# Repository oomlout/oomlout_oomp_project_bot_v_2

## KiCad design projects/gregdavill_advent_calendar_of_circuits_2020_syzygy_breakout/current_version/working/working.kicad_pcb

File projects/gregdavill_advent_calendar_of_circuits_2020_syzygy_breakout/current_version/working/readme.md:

# advent_calendar_of_circuits_2020
 
## summary 
* id: gregdavill_advent_calendar_of_circuits_2020_syzygy_breakout
* user: gregdavill
* name: advent_calendar_of_circuits_2020
* board: syzygy_breakout
* repo: https://github.com/gregdavill/advent-calendar-of-circuits-2020
* src_file_repo_kicad_pcb: syzygy-breakout/kicad-src/syzygy-breakout.kicad_pcb
* src_file_repo_kicad_pcb_link: https://github.com/gregdavill/advent-calendar-of-circuits-2020/tree/main/syzygy-breakout/kicad-src/syzygy-breakout.kicad_pcb
* src_file_repo_kicad_sch: syzygy-breakout/kicad-src/p-mcu.kicad_sch
* src_file_repo_kicad_sch_link: https://github.com/gregdavill/advent-calendar-of-circuits-2020/tree/main/syzygy-breakout/kicad-src/p-mcu.kicad_sch

* src_file_repo_sch: 
* src_file_repo_sch_link: https://github.com/gregdavill/advent-calendar-of-circuits-2020/tree/main/
* full details link: https://github.com/oomlout/oomlout_oomp_project_bot_v_2/tree/main/projects/gregdavill_advent_calendar_of_circuits_2020_syzygy_breakout/current_version/working

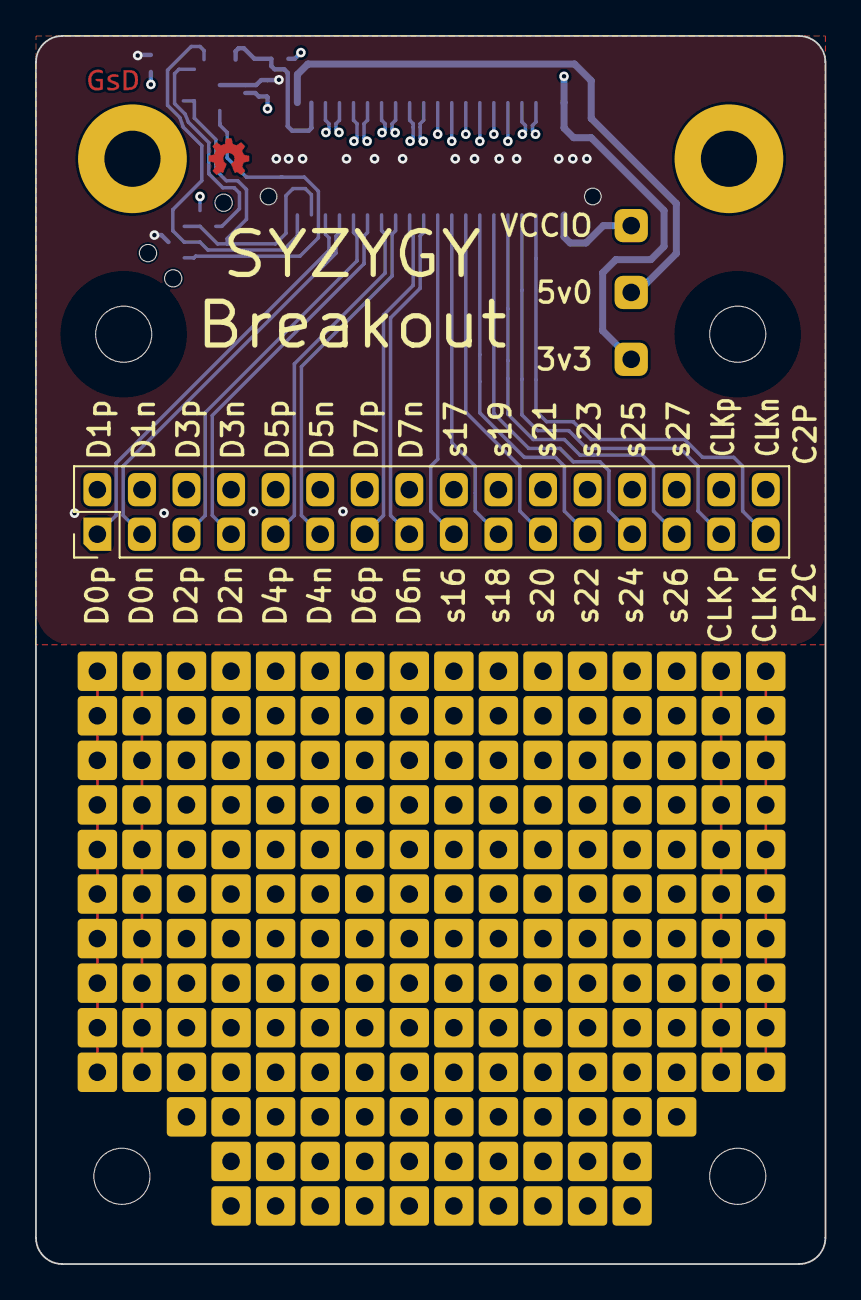
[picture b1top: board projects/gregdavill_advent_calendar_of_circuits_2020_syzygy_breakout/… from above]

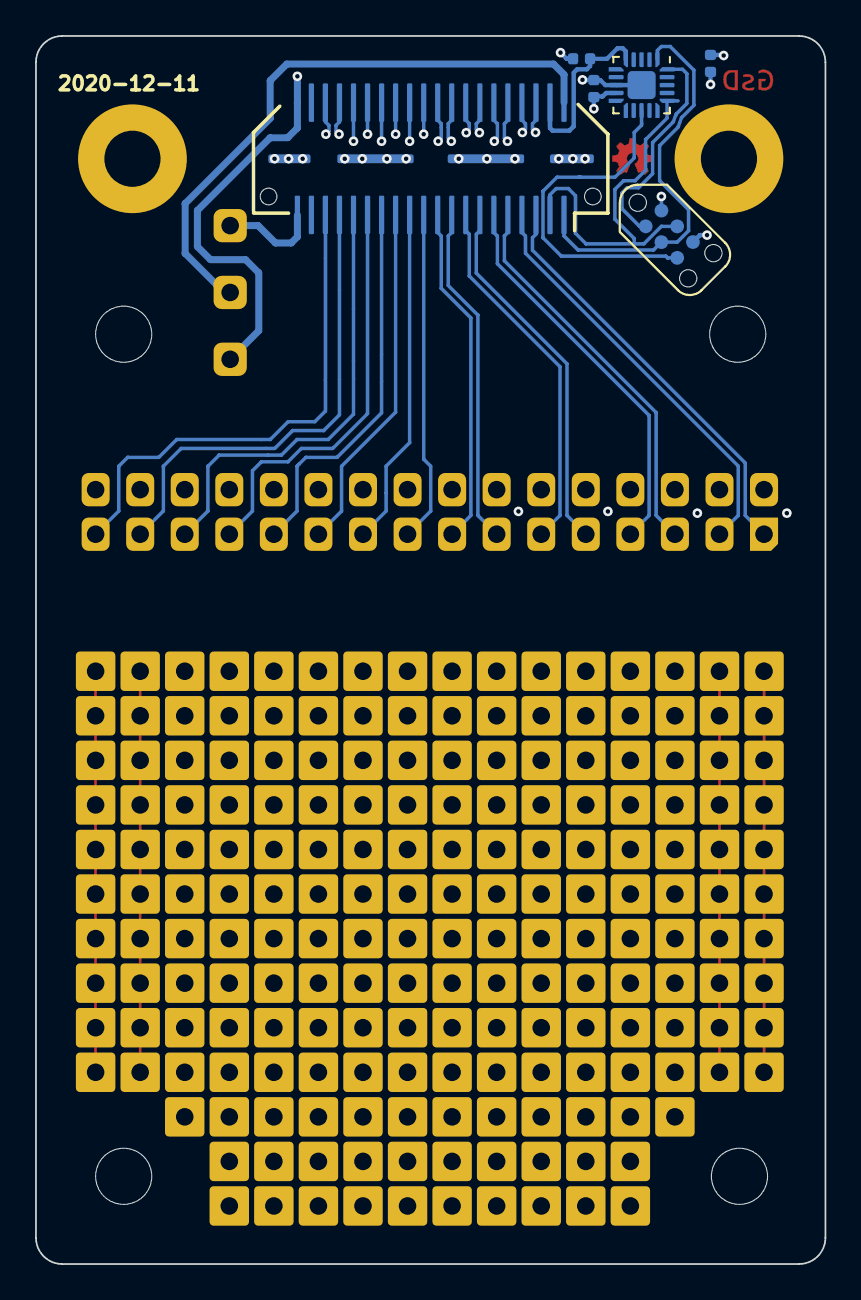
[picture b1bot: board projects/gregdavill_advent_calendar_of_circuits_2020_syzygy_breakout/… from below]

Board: 4 copper layers, 45.0 x 70.0 mm, 14 parts (6 on the bottom side), 41 nets.

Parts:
C9: 0.1uF; C_0402_1005Metric
C10: 1uF; C_0402_1005Metric
H1, H2, H3, H4: MountingHole; MountingHole_3.2mm_M3_DIN965
J1: SYZYGY-STD; SYZYGY-STD-POD
J2: Conn_02x16_Odd_Even; PinHeader_2x16_P2.54mm_Vertical
J3: TagConnect; TC2030-NL_SMALL
J4, J5, J6: Conn_01x01_Male; PinHeader_1x01_P2.54mm_Vertical
R15: 10K; R_0402_1005Metric
U2: ATtiny44A-MMH; QFN-20-1EP_3x3mm_P0.45mm_EP1.6x1.6mm

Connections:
+3V3: C9.1, C10.1, J1.40 (+3.3V), J3.2, J5.1, R15.1, U2.9 (VCC)
+5V: J1.2 (+5V), J4.1
/C2P_CLK_N: J1.36 (C2P_CLKN), J2.32
/C2P_CLK_P: J1.34 (C2P_CLKP), J2.30
/D0_N: J1.7 (S2_D0N), J2.3
/D0_P: J1.5 (S0_D0P), J2.1
/D1_N: J1.8 (S3_D1N), J2.4
/D1_P: J1.6 (S1_D1P), J2.2
/D2_N: J1.11 (S6_D2N), J2.7
/D2_P: J1.9 (S4_D2P), J2.5
/D3_N: J1.12 (S7_D3N), J2.8
/D3_P: J1.10 (S5_D3P), J2.6
/D4_N: J1.15 (S10_D4N), J2.11
/D4_P: J1.13 (S8_D4P), J2.9
/D5_N: J1.16 (S11_D5N), J2.12
/D5_P: J1.14 (S9_D5P), J2.10
/D6_N: J1.19 (S14_D6N), J2.15
/D6_P: J1.17 (S12_D6P), J2.13
/D7_N: J1.20 (S15_D7N), J2.16
/D7_P: J1.18 (S13_D7P), J2.14
/P2C_CLK_N: J1.35 (P2C_CLKN), J2.31
/P2C_CLK_P: J1.33 (P2C_CLKP), J2.29
/Peripheral MCU/MISO: J3.1, U2.20 (PA5)
/Peripheral MCU/~RESET: J3.5, U2.13 (~RESET~/PB3)
/RGA: J1.4 (R_GA), R15.2, U2.5 (AREF/PA0)
/S16: J1.21 (S16), J2.17
/S17: J1.22 (S17), J2.18
/S18: J1.23 (S18), J2.19
/S19: J1.24 (S19), J2.20
/S20: J1.25 (S20), J2.21
/S21: J1.26 (S21), J2.22
/S22: J1.27 (S22), J2.23
/S23: J1.28 (S23), J2.24
/S24: J1.29 (S24), J2.25
/S25: J1.30 (S25), J2.26
/S26: J1.31 (S26), J2.27
/S27: J1.32 (S27), J2.28
/SCL: J1.1 (SCL), J3.3, U2.1 (PA4)
/SDA: J1.3 (SDA), J3.4, U2.16 (PA6)
/VCCIO: J1.39 (VIO1), J6.1
GND: C9.2, C10.2, J1.41 (GND), J3.6, U2.8 (GND), U2.21 (GND)

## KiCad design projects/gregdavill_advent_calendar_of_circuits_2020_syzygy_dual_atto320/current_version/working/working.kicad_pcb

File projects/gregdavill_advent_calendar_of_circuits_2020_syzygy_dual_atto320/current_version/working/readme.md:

# advent_calendar_of_circuits_2020
 
## summary 
* id: gregdavill_advent_calendar_of_circuits_2020_syzygy_dual_atto320
* user: gregdavill
* name: advent_calendar_of_circuits_2020
* board: syzygy_dual_atto320
* repo: https://github.com/gregdavill/advent-calendar-of-circuits-2020
* src_file_repo_kicad_pcb: syzygy-dual-atto320/kicad-src/syzygy-dual-atto320.kicad_pcb
* src_file_repo_kicad_pcb_link: https://github.com/gregdavill/advent-calendar-of-circuits-2020/tree/main/syzygy-dual-atto320/kicad-src/syzygy-dual-atto320.kicad_pcb
* src_file_repo_kicad_sch: syzygy-dual-atto320/kicad-src/p-mcu.kicad_sch
* src_file_repo_kicad_sch_link: https://github.com/gregdavill/advent-calendar-of-circuits-2020/tree/main/syzygy-dual-atto320/kicad-src/p-mcu.kicad_sch

* src_file_repo_sch: 
* src_file_repo_sch_link: https://github.com/gregdavill/advent-calendar-of-circuits-2020/tree/main/
* full details link: https://github.com/oomlout/oomlout_oomp_project_bot_v_2/tree/main/projects/gregdavill_advent_calendar_of_circuits_2020_syzygy_dual_atto320/current_version/working

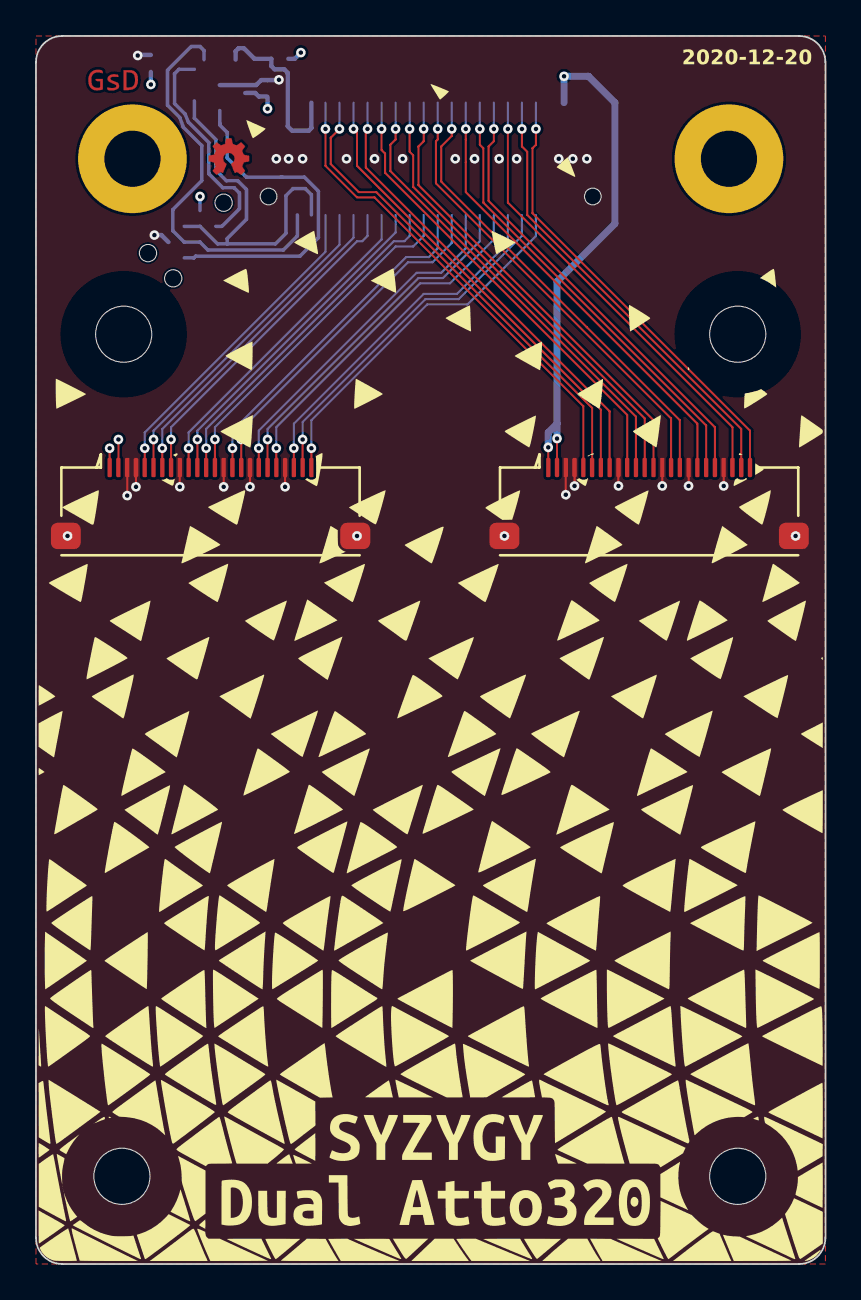
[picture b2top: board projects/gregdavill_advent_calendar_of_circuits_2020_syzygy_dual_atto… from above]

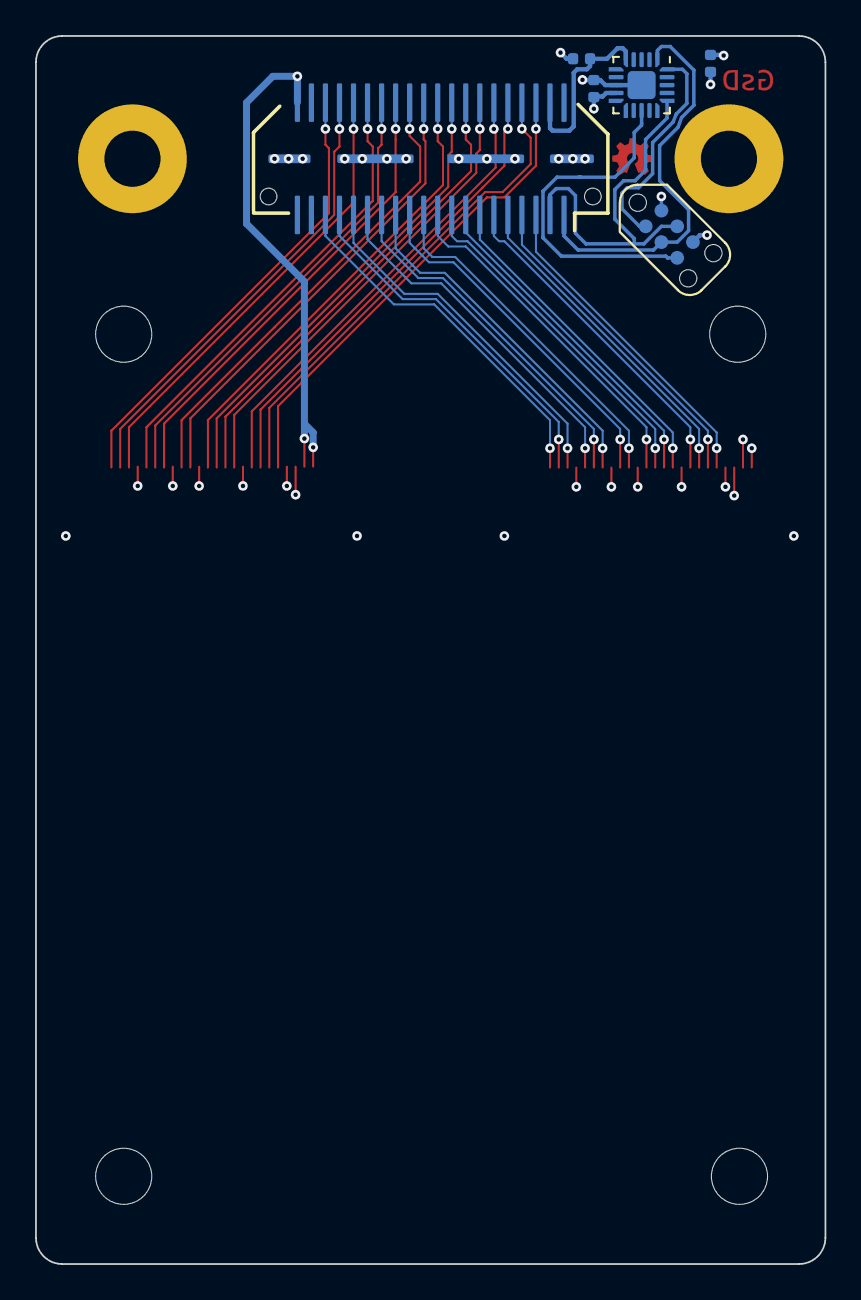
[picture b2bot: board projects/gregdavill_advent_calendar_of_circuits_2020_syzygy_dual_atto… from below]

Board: 4 copper layers, 45.0 x 70.0 mm, 12 parts (6 on the bottom side), 39 nets.

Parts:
C9: 0.1uF; C_0402_1005Metric
C10: 1uF; C_0402_1005Metric
H1, H2, H3, H4: MountingHole; MountingHole_3.2mm_M3_DIN965
J1: SYZYGY-STD; SYZYGY-STD-POD
J2, J4: Conn_01x24_MountingPin; XF2M-2415-1A
J3: TagConnect; TC2030-NL_SMALL
R15: 10K; R_0402_1005Metric
U2: ATtiny44A-MMH; QFN-20-1EP_3x3mm_P0.45mm_EP1.6x1.6mm

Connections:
+3V3: C9.1, C10.1, J1.40 (+3.3V), J2.1, J2.2, J3.2, J4.1, J4.2, R15.1, U2.9 (VCC)
/A0_CAM_SCL: J1.23 (S18), J2.16
/A0_CAM_SDA: J1.21 (S16), J2.15
/A0_DAT0: J1.5 (S0_D0P), J2.5
/A0_DAT1: J1.7 (S2_D0N), J2.6
/A0_DAT2: J1.9 (S4_D2P), J2.7
/A0_DAT3: J1.11 (S6_D2N), J2.8
/A0_DAT4: J1.13 (S8_D4P), J2.10
/A0_DAT5: J1.15 (S10_D4N), J2.11
/A0_DAT6: J1.17 (S12_D6P), J2.12
/A0_DAT7: J1.19 (S14_D6N), J2.13
/A0_HSYNC: J1.27 (S22), J2.19
/A0_MCLK: J1.31 (S26), J2.22
/A0_NRST: J1.33 (P2C_CLKP), J2.23
/A0_PSYNC: J1.25 (S20), J2.18
/A0_SEQ_TRIG: J1.35 (P2C_CLKN), J2.24
/A0_VSYNC: J1.29 (S24), J2.20
/A1_CAM_SCL: J1.24 (S19), J4.16
/A1_CAM_SDA: J1.22 (S17), J4.15
/A1_DAT0: J1.6 (S1_D1P), J4.5
/A1_DAT1: J1.8 (S3_D1N), J4.6
/A1_DAT2: J1.10 (S5_D3P), J4.7
/A1_DAT3: J1.12 (S7_D3N), J4.8
/A1_DAT4: J1.14 (S9_D5P), J4.10
/A1_DAT5: J1.16 (S11_D5N), J4.11
/A1_DAT6: J1.18 (S13_D7P), J4.12
/A1_DAT7: J1.20 (S15_D7N), J4.13
/A1_HSYNC: J1.28 (S23), J4.19
/A1_MCLK: J1.32 (S27), J4.22
/A1_NRST: J1.34 (C2P_CLKP), J4.23
/A1_PSYNC: J1.26 (S21), J4.18
/A1_SEQ_TRIG: J1.36 (C2P_CLKN), J4.24
/A1_VSYNC: J1.30 (S25), J4.20
/Peripheral MCU/MISO: J3.1, U2.20 (PA5)
/Peripheral MCU/~RESET: J3.5, U2.13 (~RESET~/PB3)
/RGA: J1.4 (R_GA), R15.2, U2.5 (AREF/PA0)
/SCL: J1.1 (SCL), J3.3, U2.1 (PA4)
/SDA: J1.3 (SDA), J3.4, U2.16 (PA6)
GND: C9.2, C10.2, J1.41 (GND), J2.3, J2.4, J2.9, J2.14, J2.17, J2.21, J2.MP (MountPin), J3.6, J4.3, J4.4, J4.9, J4.14, J4.17, J4.21, J4.MP (MountPin), U2.8 (GND), U2.21 (GND)

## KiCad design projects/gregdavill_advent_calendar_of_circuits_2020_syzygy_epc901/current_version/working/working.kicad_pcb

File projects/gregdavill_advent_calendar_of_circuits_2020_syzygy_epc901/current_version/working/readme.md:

# advent_calendar_of_circuits_2020
 
## summary 
* id: gregdavill_advent_calendar_of_circuits_2020_syzygy_epc901
* user: gregdavill
* name: advent_calendar_of_circuits_2020
* board: syzygy_epc901
* repo: https://github.com/gregdavill/advent-calendar-of-circuits-2020
* src_file_repo_kicad_pcb: syzygy-epc901/kicad-src/syzygy-epc901.kicad_pcb
* src_file_repo_kicad_pcb_link: https://github.com/gregdavill/advent-calendar-of-circuits-2020/tree/main/syzygy-epc901/kicad-src/syzygy-epc901.kicad_pcb
* src_file_repo_kicad_sch: syzygy-epc901/kicad-src/epc901.kicad_sch
* src_file_repo_kicad_sch_link: https://github.com/gregdavill/advent-calendar-of-circuits-2020/tree/main/syzygy-epc901/kicad-src/epc901.kicad_sch

* src_file_repo_sch: 
* src_file_repo_sch_link: https://github.com/gregdavill/advent-calendar-of-circuits-2020/tree/main/
* full details link: https://github.com/oomlout/oomlout_oomp_project_bot_v_2/tree/main/projects/gregdavill_advent_calendar_of_circuits_2020_syzygy_epc901/current_version/working

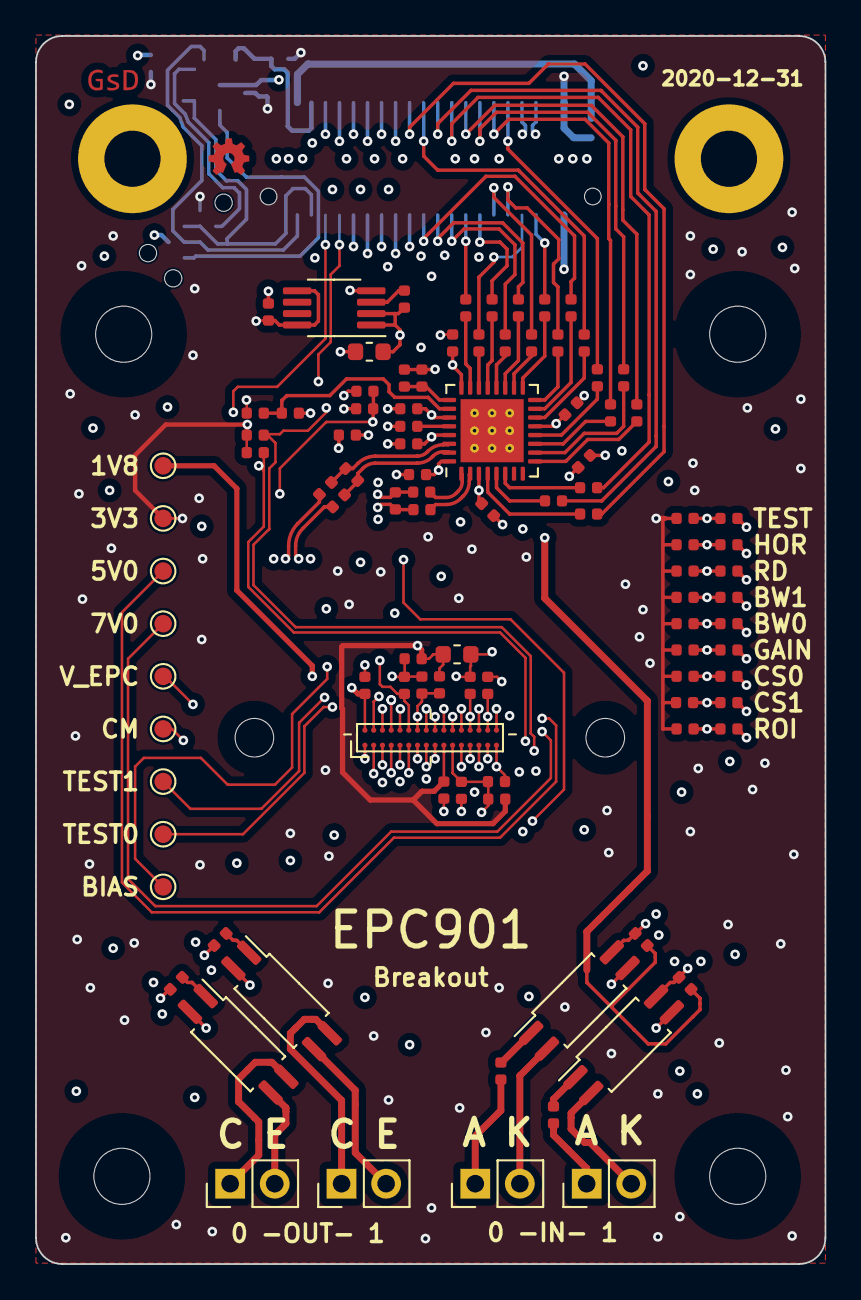
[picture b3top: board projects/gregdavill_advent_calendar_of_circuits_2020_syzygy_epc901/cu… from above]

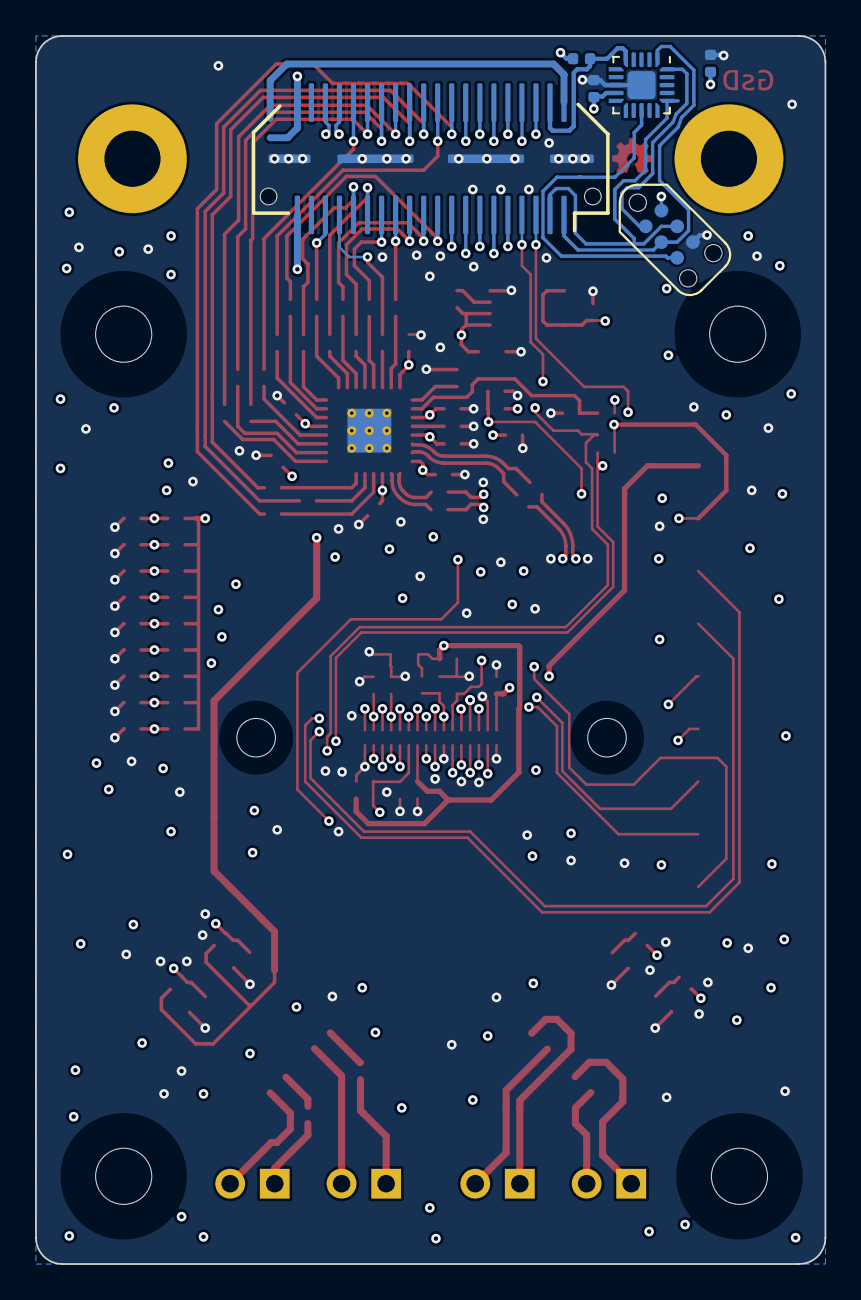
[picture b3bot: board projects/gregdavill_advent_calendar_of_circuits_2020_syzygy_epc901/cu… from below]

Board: 4 copper layers, 45.0 x 70.0 mm, 110 parts (6 on the bottom side), 96 nets.

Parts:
C1, C4, C5, C9, C11, C20, C21, C22, C23, C24, C26: 0.1uF; C_0402_1005Metric
C2, C6, C7, C10, C13, C16, C19, C25: 1uF; C_0402_1005Metric
C3: 22pF; C_0402_1005Metric
C8, C18: 10uF; C_0603_1608Metric
C12: DNP; C_0402_1005Metric
C14, C15: 2.2uF; C_0402_1005Metric
C17: 0.01uF; C_0402_1005Metric
H1, H2, H3, H4: MountingHole; MountingHole_3.2mm_M3_DIN965
H5: LensMount; lensholder-m12-20mm
J1: SYZYGY-STD; SYZYGY-STD-POD
J2, J4, J5, J6: Conn_01x02_Male; PinHeader_1x02_P2.54mm_Vertical
J3: TagConnect; TC2030-NL_SMALL
L1: 600R @100M; L_0402_1005Metric
R1, R11, R12, R13, R14, R16, R17, R18, R19, R20, R21, R26, R27, R28, R29, R30, R31: DNP; R_0402_1005Metric
R2, R23, R24, R25, R32: 0R; R_0402_1005Metric
R3, R4: 33R; R_0402_1005Metric
R5, R6, R7, R8, R35, R36, R37, R38, R39, R40, R41, R42, R43, R44, R45, R46, R47, R48, R52, R53, R54, R55: 100R; R_0402_1005Metric
R9, R10, R50, R51: 2K2; R_0402_1005Metric
R15, R49: 10K; R_0402_1005Metric
R22: 56K 1% 100ppm/K; R_0402_1005Metric
R33, R34: 1K; R_0402_1005Metric
TP1, TP3, TP4, TP5, TP6, TP7, TP8, TP9, TP10: TestPoint; TestPoint_Pad_D1.0mm
U1: AD9629; QFN-32-1EP_5x5mm_P0.5mm_EP3.6x3.6mm_ThermalVias
U2: ATtiny44A-MMH; QFN-20-1EP_3x3mm_P0.45mm_EP1.6x1.6mm
U3: EPC901; epc901
U4: LT1962-1.8; MSOP-8_3x3mm_P0.65mm
U5, U6, U7, U8: TLP291; SOIC-4_4.55x2.6mm_P1.27mm

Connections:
+3V3: C7.1, C8.1, C9.1, C10.1, C11.1, C16.1, J1.40 (+3.3V), J3.2, L1.2, R1.1, R9.1, R10.1, R11.1, R12.1, R13.1, R14.1, R15.1, R16.1, R23.1, R24.1, R25.1, R26.1, R31.1, TP1.1, U2.9 (VCC), U3.10 (VDD_OA), U4.5 (~SHDN), U4.8 (IN)
/1V8: C17.1, C18.1, C19.1, C20.1, C21.1, C22.1, C23.1, R33.1, U1.3 (AVDD), U1.24 (AVDD), U1.29 (AVDD), U1.32 (AVDD), U4.1 (OUT), U4.2 (SENSE)
/ADC_CLK_N: C5.1, J1.34 (C2P_CLKP), R5.1
/ADC_CLK_P: C4.1, J1.36 (C2P_CLKN), R5.2
/ADC_CS: J1.18 (S13_D7P), R6.2
/ADC_D0: J1.26 (S21), R35.1
/ADC_D1: J1.28 (S23), R36.1
/ADC_D2: J1.30 (S25), R37.1
/ADC_D3: J1.32 (S27), R38.1
/ADC_D4: J1.20 (S15_D7N), R39.1
/ADC_D5: J1.19 (S14_D6N), R40.1
/ADC_D6: J1.31 (S26), R41.1
/ADC_D7: J1.35 (P2C_CLKN), R42.1
/ADC_D8: J1.29 (S24), R43.1
/ADC_D9: J1.21 (S16), R44.1
/ADC_D10: J1.23 (S18), R45.1
/ADC_D11: J1.27 (S22), R46.1
/ADC_DCO: J1.33 (P2C_CLKP), R47.1
/ADC_MODE: J1.25 (S20), R48.2
/ADC_N: C3.2, R4.1, U1.30 (VIN-)
/ADC_P: C3.1, R3.2, U1.31 (VIN+)
/ADC_SCLK: J1.22 (S17), R7.2
/ADC_SDIO: J1.24 (S19), R8.2
/CLK_N: C5.2, U1.2 (CLK-)
/CLK_P: C4.2, U1.1 (CLK+)
/OPTO_IN0: J1.10 (S5_D3P), R50.2, U8.4
/OPTO_IN1: J1.8 (S3_D1N), R51.2, U6.4
/OPTO_OUT0: J1.12 (S7_D3N), R52.2
/OPTO_OUT1: J1.14 (S9_D5P), R54.2
/Peripheral MCU/MISO: J3.1, U2.20 (PA5)
/Peripheral MCU/~RESET: J3.5, U2.13 (~RESET~/PB3)
/RGA: J1.4 (R_GA), R15.2, U2.5 (AREF/PA0)
/SCL: J1.1 (SCL), J3.3, U2.1 (PA4)
/SDA: J1.3 (SDA), J3.4, U2.16 (PA6)
/SENSE: R1.2, R2.1, U1.26 (SENSE)
/VCCIO: C24.1, C25.1, J1.39 (VIO1), R50.1, R51.1, U1.13 (DRVDD)
/epc901/ANA_TEST1: TP8.1, U3.28 (ANA_TEST_1)
/epc901/ANA_TEST2: TP9.1, U3.29 (ANA_TEST_0)
/epc901/BW0: R23.2, R27.1, U3.22 (BW0)
/epc901/BW1: R24.2, R28.1, U3.23 (BW1)
/epc901/CS0: R14.2, R20.1, U3.19 (CS0)
/epc901/CS1: R13.2, R19.1, U3.17 (CS1)
/epc901/EPC_VDD: C6.1, L1.1, TP3.1, U3.26 (VDD)
/epc901/GAIN: R16.2, R21.1, U3.21 (GAIN)
/epc901/HOR_BIN: R26.2, R30.1, U3.25 (HOR_BIN)
/epc901/I_BIAS: R22.1, TP7.1, U3.27 (I_BIAS)
/epc901/RD_DIR: R25.2, R29.1, U3.24 (RD_DIR)
/epc901/ROI_SEL: R12.2, R18.1, U3.15 (ROI_SEL)
/epc901/TEST_MODE: R31.2, R32.1, U3.30 (TEST_MODE)
/epc901/VDD_1V8: C13.1, TP4.1, U3.32 (VDD1V8)
/epc901/VDD_5V0: C14.1, TP5.1, U3.18 (VDD5V0)
/epc901/VDD_7V0: C15.1, TP6.1, U3.20 (VDD7V0)
CLR_DATA: J1.13 (S8_D4P), U3.3 (CLR_DATA)
CLR_PIX: J1.15 (S10_D4N), U3.5 (CLR_PIX)
DATA_RDY: J1.9 (S4_D2P), U3.4 (DATA_RDY)
EPC_SCL: J1.7 (S2_D0N), R10.2, U3.14 (SCL)
EPC_SDA: J1.5 (S0_D0P), R9.2, U3.13 (SDA)
EXT_ADC_CM: C12.1, C26.1, R11.2, R17.1, R33.2, R34.1, TP10.1, U1.27 (VCM), U3.11 (VIDEO_CM)
EXT_ADC_N: R4.2, U3.8 (VIDEO_N)
EXT_ADC_P: R3.1, U3.9 (VIDEO_P)
GND: C1.2, C2.2, C6.2, C7.2, C8.2, C9.2, C10.2, C11.2, C12.2, C13.2, C14.2, C15.2, C16.2, C18.2, C19.2, C20.2, C21.2, C22.2, C23.2, C24.2, C25.2, C26.2, J1.41 (GND), J3.6, R2.2, R17.2, R18.2, R19.2, R20.2, R21.2, R22.2, R27.2, R28.2, R29.2, R30.2, R32.2, R34.2, R49.2, U1.33 (GND), U2.8 (GND), U2.21 (GND), U3.1 (AGND), U3.7 (GND_OA), U3.16 (AGND), U3.31 (DGND), U4.4 (GND), U5.2, U6.3, U7.2, U8.3
unnamed: C1.1, C2.1, U1.25 (VREF)
unnamed: C17.2, U4.3 (BYP)
unnamed: J2.1, U5.4
unnamed: J2.2, U5.3
unnamed: J4.1, R53.2
unnamed: J4.2, U6.2
unnamed: J5.1, U7.4
unnamed: J5.2, U7.3
unnamed: J6.1, R55.2
unnamed: J6.2, U8.2
unnamed: R6.1, U1.4 (CSB)
unnamed: R7.1, U1.5 (SCLK/DFS)
unnamed: R8.1, U1.6 (SDIO/PDWN)
unnamed: R35.2, U1.9 (D0)
unnamed: R36.2, U1.10 (D1)
unnamed: R37.2, U1.11 (D2)
unnamed: R38.2, U1.12 (D3)
unnamed: R39.2, U1.14 (D4)
unnamed: R40.2, U1.15 (D5)
unnamed: R41.2, U1.16 (D6)
unnamed: R42.2, U1.17 (D7)
unnamed: R43.2, U1.18 (D8)
unnamed: R44.2, U1.19 (D9)
unnamed: R45.2, U1.20 (D10)
unnamed: R46.2, U1.21 (D11)
unnamed: R47.2, U1.22 (DCO)
unnamed: R48.1, U1.23 (MODE/OR)
unnamed: R49.1, U1.28 (RBIAS)
unnamed: R52.1, U5.1
unnamed: R53.1, U6.1
unnamed: R54.1, U7.1
unnamed: R55.1, U8.1
PWR_DOWN: J1.11 (S6_D2N), U3.2 (PWR_DOWN)
READ: J1.6 (S1_D1P), U3.12 (READ)
SHUTTER: J1.17 (S12_D6P), U3.6 (SHUTTER)

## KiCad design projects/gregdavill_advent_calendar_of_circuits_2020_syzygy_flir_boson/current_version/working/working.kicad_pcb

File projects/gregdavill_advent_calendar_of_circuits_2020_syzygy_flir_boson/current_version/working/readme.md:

# advent_calendar_of_circuits_2020
 
## summary 
* id: gregdavill_advent_calendar_of_circuits_2020_syzygy_flir_boson
* user: gregdavill
* name: advent_calendar_of_circuits_2020
* board: syzygy_flir_boson
* repo: https://github.com/gregdavill/advent-calendar-of-circuits-2020
* src_file_repo_kicad_pcb: syzygy-flir-boson/kicad-src/syzygy-flir-boson.kicad_pcb
* src_file_repo_kicad_pcb_link: https://github.com/gregdavill/advent-calendar-of-circuits-2020/tree/main/syzygy-flir-boson/kicad-src/syzygy-flir-boson.kicad_pcb
* src_file_repo_kicad_sch: syzygy-flir-boson/kicad-src/p-mcu.kicad_sch
* src_file_repo_kicad_sch_link: https://github.com/gregdavill/advent-calendar-of-circuits-2020/tree/main/syzygy-flir-boson/kicad-src/p-mcu.kicad_sch

* src_file_repo_sch: 
* src_file_repo_sch_link: https://github.com/gregdavill/advent-calendar-of-circuits-2020/tree/main/
* full details link: https://github.com/oomlout/oomlout_oomp_project_bot_v_2/tree/main/projects/gregdavill_advent_calendar_of_circuits_2020_syzygy_flir_boson/current_version/working

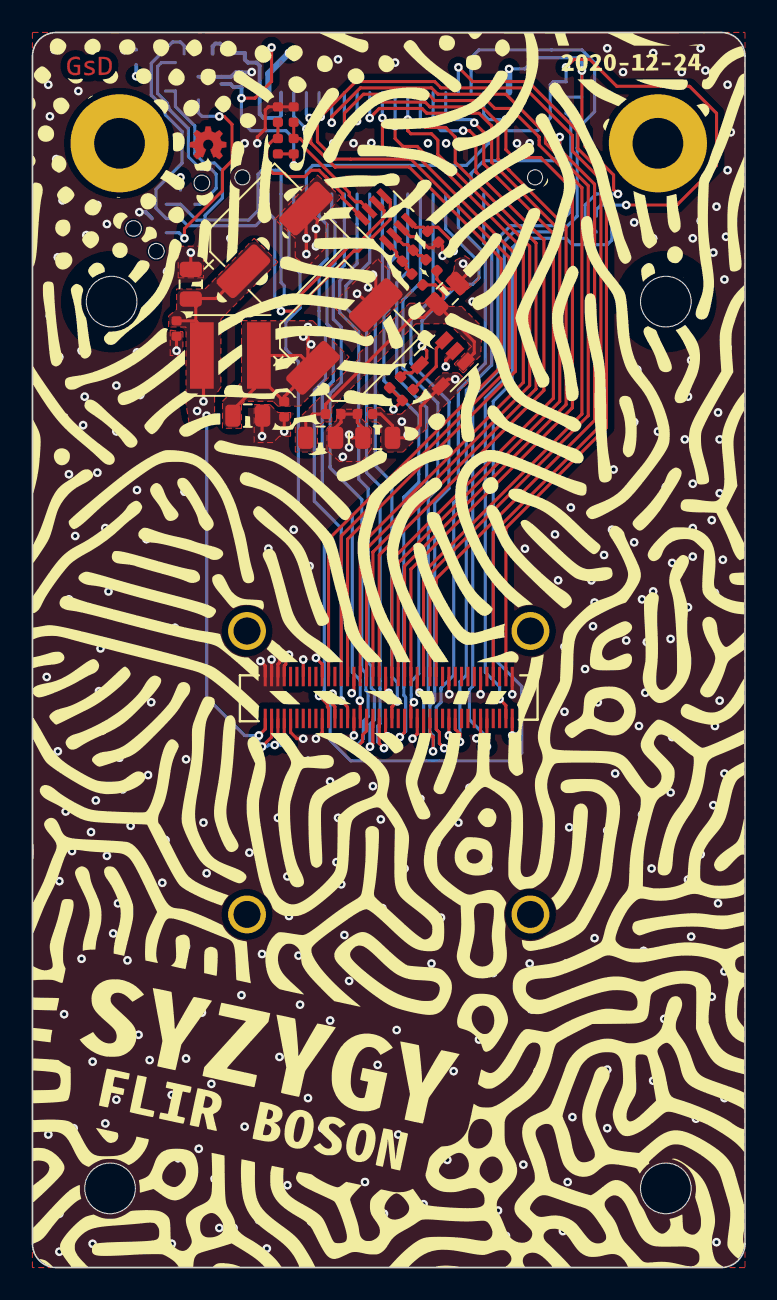
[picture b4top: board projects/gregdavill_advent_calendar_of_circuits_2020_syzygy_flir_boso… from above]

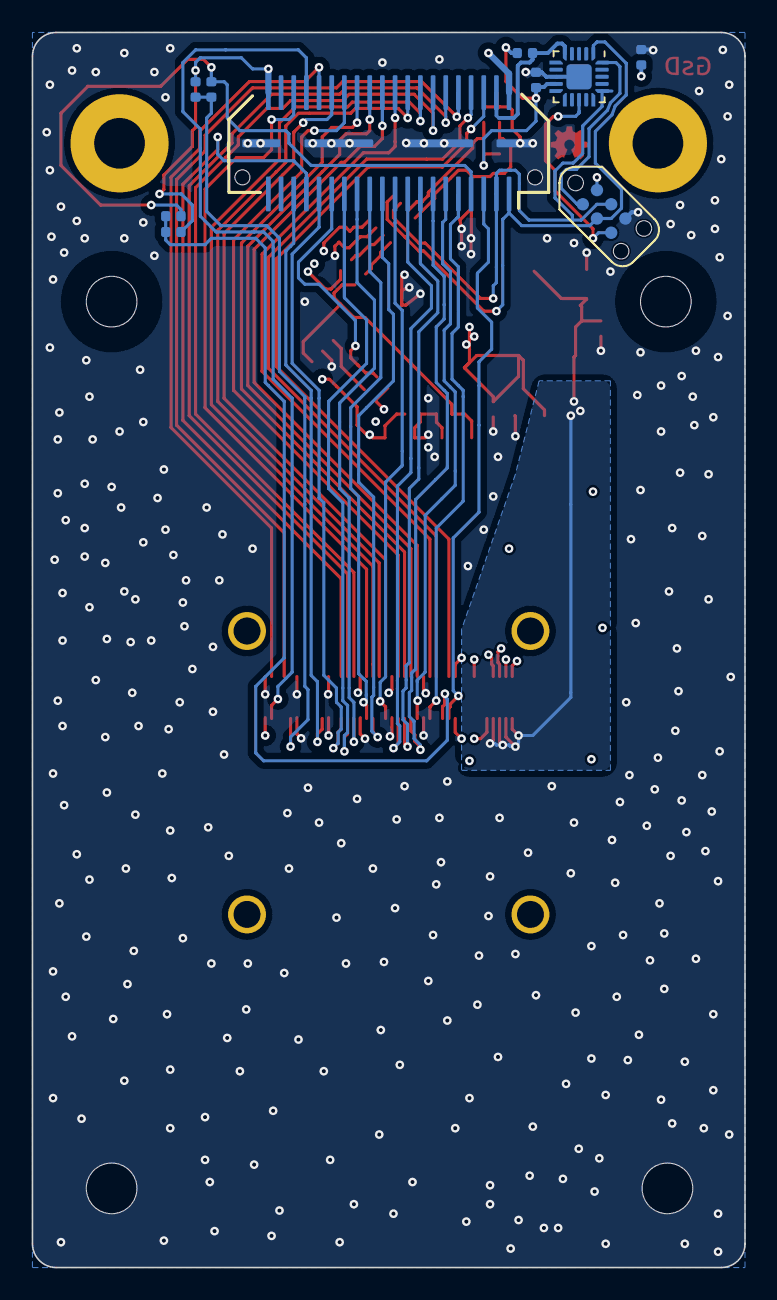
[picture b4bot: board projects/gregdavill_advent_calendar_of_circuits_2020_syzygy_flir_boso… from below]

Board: 4 copper layers, 45.0 x 78.0 mm, 43 parts (10 on the bottom side), 49 nets.

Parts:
C1, C2, C5, C8, C9, C11, C13: 0.1uF; C_0402_1005Metric
C3, C6, C12, C14: 10uF; C_0805_2012Metric
C4, C7: 120uF; CP_Elec_6.3x5.3
C10: 1uF; C_0402_1005Metric
H1, H1#3, H1#4, H1#5: MountingHole; Pin_D1.0mm_L10.0mm
H1#2, H2, H3, H4: MountingHole; MountingHole_3.2mm_M3_DIN965
J1: SYZYGY-STD; SYZYGY-STD-POD
J2: Boson; DF40_80Pin
J3: TagConnect; TC2030-NL_SMALL
L1: 22uH; L_Taiyo-Yuden_NR-50xx
R1, R2, R10, R11, R15: 10k; R_0402_1005Metric
R3, R5: 10R; R_0402_1005Metric
R4: 100m; R_0805_2012Metric
R6, R7, R13: DNP; R_0402_1005Metric
R8, R9, R12: 0R; R_0402_1005Metric
U1: TPS2061; SOT-23-5
U2: ATtiny44A-MMH; QFN-20-1EP_3x3mm_P0.45mm_EP1.6x1.6mm
U3: INA219AxDCN; SOT-23-8

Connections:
+3V3: C8.1, C9.1, C10.1, C13.1, C14.1, J1.40 (+3.3V), J3.2, R1.2, R2.2, R6.2, R7.2, R10.2, R11.2, R15.1, U1.5 (IN), U2.9 (VCC), U3.4 (VS)
/3V3_BOSON: C5.1, C6.1, C7.1, J2.2, J2.4, J2.6, J2.8, L1.2
/DATA_0: J1.32 (S27), J2.77
/DATA_1: J1.35 (P2C_CLKN), J2.62
/DATA_2: J1.14 (S9_D5P), J2.51
/DATA_3: J1.31 (S26), J2.56
/DATA_4: J1.20 (S15_D7N), J2.27
/DATA_5: J1.9 (S4_D2P), J2.28
/DATA_6: J1.11 (S6_D2N), J2.32
/DATA_7: J1.22 (S17), J2.31
/DATA_8: J1.8 (S3_D1N), J2.25
/DATA_9: J1.21 (S16), J2.46
/DATA_10: J1.16 (S11_D5N), J2.45
/DATA_11: J1.23 (S18), J2.48
/DATA_12: J1.36 (C2P_CLKN), J2.47
/DATA_13: J1.30 (S25), J2.41
/DATA_14: J1.6 (S1_D1P), J2.21
/DATA_15: J1.17 (S12_D6P), J2.38
/DATA_16: J1.13 (S8_D4P), J2.34
/DATA_17: J1.5 (S0_D0P), J2.22
/DATA_18: J1.19 (S14_D6N), J2.42
/DATA_19: J1.28 (S23), J2.37
/DATA_20: J1.25 (S20), J2.52
/DATA_21: J1.27 (S22), J2.54
/DATA_22: J1.26 (S21), J2.35
/DATA_23: J1.15 (S10_D4N), J2.36
/DATA_VALID: J1.34 (C2P_CLKP), J2.78
/EXT_SYNC: J2.72, R11.1, R13.2
/HSYNC: J1.10 (S5_D3P), J2.73
/PIX_CLK: J1.33 (P2C_CLKP), J2.55
/PWR_EN: J1.29 (S24), R1.1, U1.4 (~EN)
/PWR_OC: R2.1, U1.3 (~OC)
/Peripheral MCU/MISO: J3.1, U2.20 (PA5)
/Peripheral MCU/~RESET: J3.5, U2.13 (~RESET~/PB3)
/RESET: J2.24, R10.1, R12.1
/RGA: J1.4 (R_GA), R15.2, U2.5 (AREF/PA0)
/SCL: J1.1 (SCL), J3.3, U2.1 (PA4), U3.5 (SCL)
/SDA: J1.3 (SDA), J3.4, U2.16 (PA6), U3.6 (SDA)
/UART_RXD: J1.24 (S19), J2.33
/UART_TXD: J1.18 (S13_D7P), J2.43
/VSYNC: J1.12 (S7_D3N), J2.53
/_3V3_BOSON: C11.1, C12.1, R3.2, R4.1, U1.1 (OUT)
GND: C2.2, C3.2, C4.2, C5.2, C6.2, C7.2, C8.2, C9.2, C10.2, C11.2, C12.2, C13.2, C14.2, J1.41 (GND), J2.1, J2.3, J2.5, J2.7, J2.10, J2.13, J2.19, J2.20, J2.29, J2.30, J2.39, J2.40, J2.49, J2.50, J2.59, J2.60, J2.69, J2.70, J2.79, J3.6, R8.1, R9.1, U1.2 (GND), U2.8 (GND), U2.21 (GND), U3.3 (GND)
unnamed: C1.1, R3.1, U3.1 (IN+)
unnamed: C1.2, R5.1, U3.2 (IN-)
unnamed: C2.1, C3.1, C4.1, L1.1, R4.2, R5.2
unnamed: J1.7 (S2_D0N), R12.2, R13.1
unnamed: R6.1, R8.2, U3.8 (A1)
unnamed: R7.1, R9.2, U3.7 (A0)

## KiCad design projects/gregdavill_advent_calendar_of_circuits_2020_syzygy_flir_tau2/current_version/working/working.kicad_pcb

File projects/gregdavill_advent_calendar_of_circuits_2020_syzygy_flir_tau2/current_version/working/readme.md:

# advent_calendar_of_circuits_2020
 
## summary 
* id: gregdavill_advent_calendar_of_circuits_2020_syzygy_flir_tau2
* user: gregdavill
* name: advent_calendar_of_circuits_2020
* board: syzygy_flir_tau2
* repo: https://github.com/gregdavill/advent-calendar-of-circuits-2020
* src_file_repo_kicad_pcb: syzygy-flir-tau2/kicad-src/syzygy-flir-tau2.kicad_pcb
* src_file_repo_kicad_pcb_link: https://github.com/gregdavill/advent-calendar-of-circuits-2020/tree/main/syzygy-flir-tau2/kicad-src/syzygy-flir-tau2.kicad_pcb
* src_file_repo_kicad_sch: syzygy-flir-tau2/kicad-src/p-mcu.kicad_sch
* src_file_repo_kicad_sch_link: https://github.com/gregdavill/advent-calendar-of-circuits-2020/tree/main/syzygy-flir-tau2/kicad-src/p-mcu.kicad_sch

* src_file_repo_sch: 
* src_file_repo_sch_link: https://github.com/gregdavill/advent-calendar-of-circuits-2020/tree/main/
* full details link: https://github.com/oomlout/oomlout_oomp_project_bot_v_2/tree/main/projects/gregdavill_advent_calendar_of_circuits_2020_syzygy_flir_tau2/current_version/working

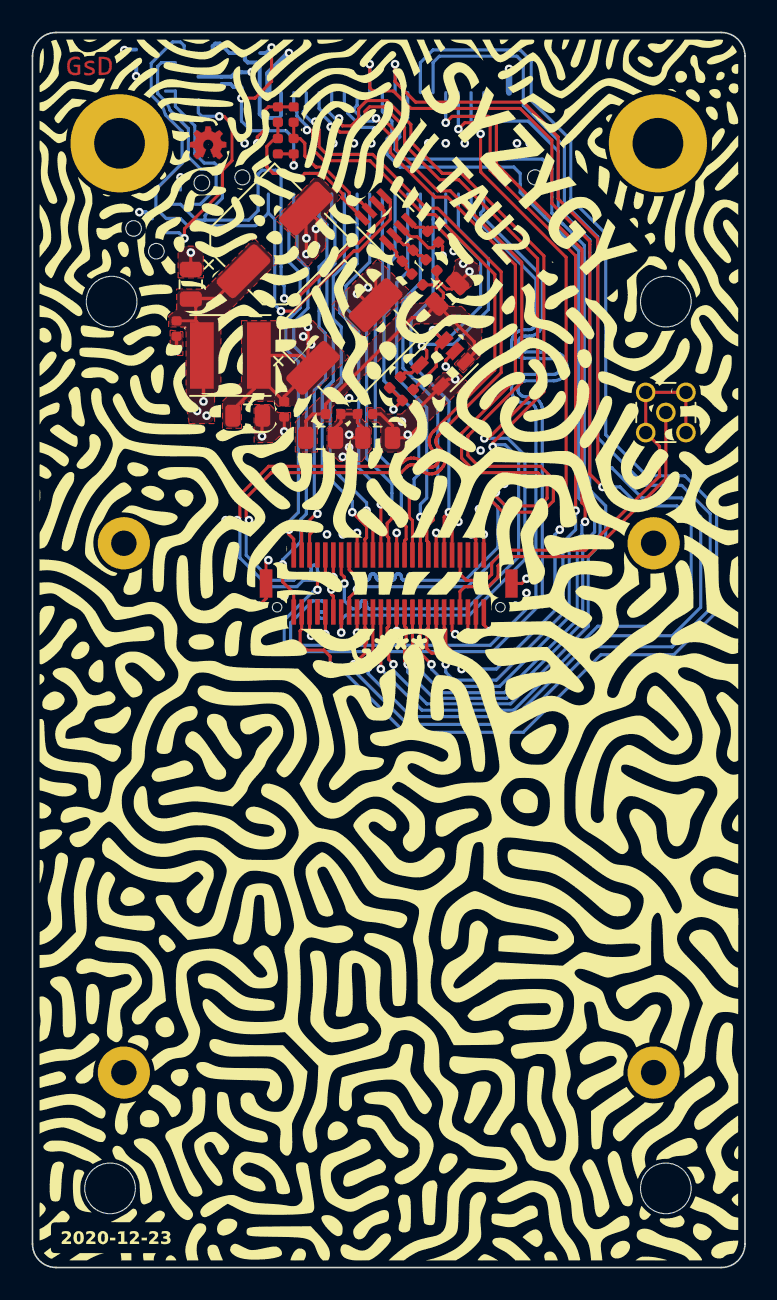
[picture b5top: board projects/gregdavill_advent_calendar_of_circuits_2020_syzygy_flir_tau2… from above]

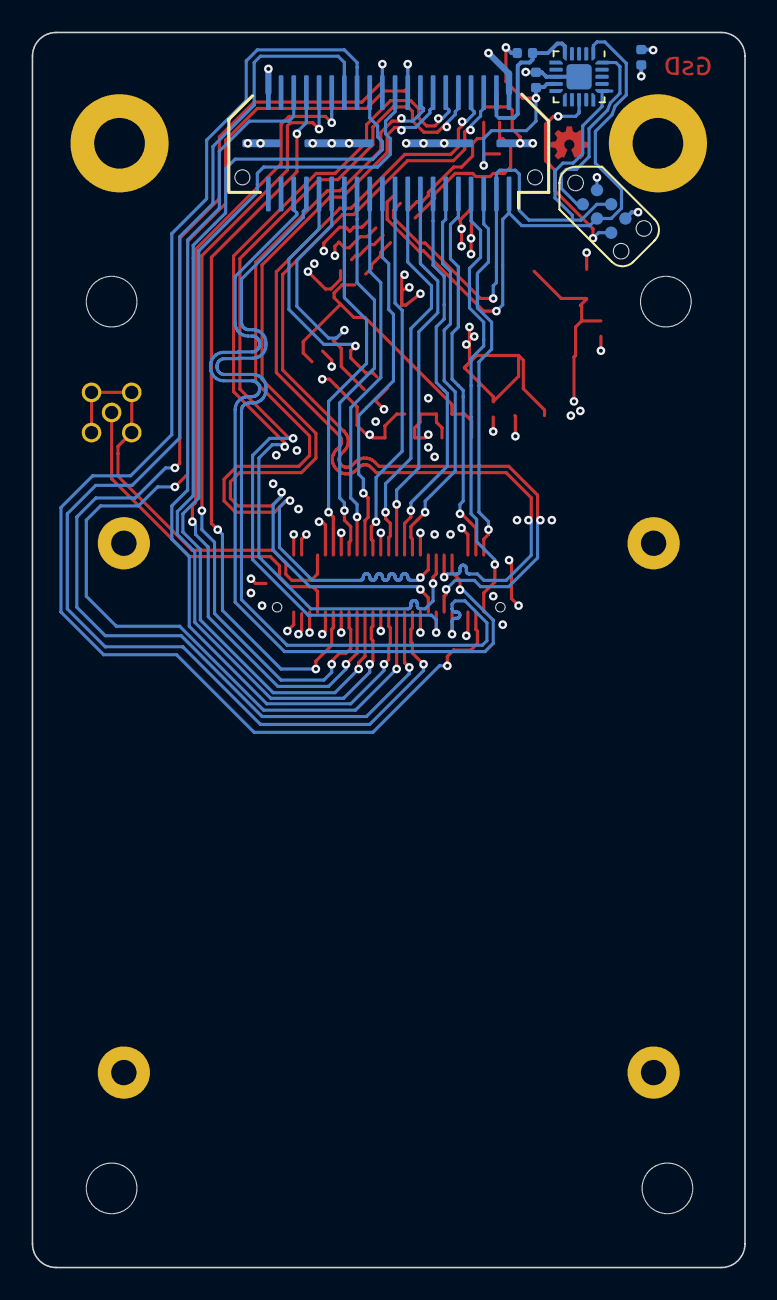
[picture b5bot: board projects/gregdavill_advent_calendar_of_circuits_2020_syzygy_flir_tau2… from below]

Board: 4 copper layers, 45.0 x 78.0 mm, 36 parts (6 on the bottom side), 49 nets.

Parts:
C1, C2, C5, C8, C9, C11, C13: 0.1uF; C_0402_1005Metric
C3, C6, C12, C14: 10uF; C_0805_2012Metric
C4, C7: 120uF; CP_Elec_6.3x5.3
C10: 1uF; C_0402_1005Metric
H1, H2, H3, H4: MountingHole; MountingHole_3.2mm_M3_DIN965
J1: SYZYGY-STD; SYZYGY-STD-POD
J2: Conn_02x25_Odd_Even; DF12(5.0)-50DP
J3: TagConnect; TC2030-NL_SMALL
J4: Conn_Coaxial; MMCX_Molex_73415-1471_Vertical
L1: 22uH; L_Taiyo-Yuden_NR-50xx
R1, R2: 10k; R_0402_1005Metric
R3, R5: 10R; R_0402_1005Metric
R4: 100m; R_0805_2012Metric
R6, R7: DNP; R_0402_1005Metric
R8, R9: 0R; R_0402_1005Metric
R15: 10K; R_0402_1005Metric
U1: TPS2061; SOT-23-5
U2: ATtiny44A-MMH; QFN-20-1EP_3x3mm_P0.45mm_EP1.6x1.6mm
U3: INA219AxDCN; SOT-23-8

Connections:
+3V3: C8.1, C9.1, C10.1, J1.40 (+3.3V), J3.2, R1.2, R2.2, R6.2, R7.2, R15.1, U2.9 (VCC), U3.4 (VS)
+5V: C13.1, C14.1, J1.2 (+5V), U1.5 (IN)
/LVDS_CLK_N: J1.35 (P2C_CLKN), J2.10
/LVDS_CLK_P: J1.33 (P2C_CLKP), J2.9
/LVDS_DATA1_N: J1.12 (S7_D3N), J2.14
/LVDS_DATA1_P: J1.10 (S5_D3P), J2.13
/LVDS_DATA2_N: J1.16 (S11_D5N), J2.16
/LVDS_DATA2_P: J1.14 (S9_D5P), J2.15
/LVDS_SYNC_N: J1.8 (S3_D1N), J2.12
/LVDS_SYNC_P: J1.6 (S1_D1P), J2.11
/MAIN_POWER: C5.1, C6.1, C7.1, J2.48, J2.50, L1.2
/Peripheral MCU/MISO: J3.1, U2.20 (PA5)
/Peripheral MCU/~RESET: J3.5, U2.13 (~RESET~/PB3)
/RGA: J1.4 (R_GA), R15.2, U2.5 (AREF/PA0)
/RS232_RX: J1.5 (S0_D0P), J2.2
/RS232_TX: J1.7 (S2_D0N), J2.1
/SCL: J1.1 (SCL), J3.3, U2.1 (PA4), U3.5 (SCL)
/SDA: J1.3 (SDA), J3.4, U2.16 (PA6), U3.6 (SDA)
/TAU_5V: C11.1, C12.1, R3.2, R4.1, U1.1 (OUT)
/TAU_PWR_EN: J1.31 (S26), R1.1, U1.4 (~EN)
/TAU_PWR_OC: J1.29 (S24), R2.1, U1.3 (~OC)
/VIDEO_N: J2.44, J4.2 (Ext)
/VIDEO_P: J2.43, J4.1 (In)
/XP_CLK1: J1.34 (C2P_CLKP), J2.39
/XP_CLK2: J1.27 (S22), J2.40
/XP_D0: J1.25 (S20), J2.36
/XP_D1: J1.32 (S27), J2.35
/XP_D2: J1.23 (S18), J2.34
/XP_D3: J1.30 (S25), J2.33
/XP_D4: J1.21 (S16), J2.32
/XP_D5: J1.20 (S15_D7N), J2.31
/XP_D6: J1.19 (S14_D6N), J2.30
/XP_D7: J1.24 (S19), J2.29
/XP_D8: J1.17 (S12_D6P), J2.26
/XP_D9: J1.36 (C2P_CLKN), J2.25
/XP_D10: J1.15 (S10_D4N), J2.24
/XP_D11: J1.18 (S13_D7P), J2.23
/XP_D12: J1.13 (S8_D4P), J2.22
/XP_D13: J1.22 (S17), J2.21
/XP_D14: J1.11 (S6_D2N), J2.20
/XP_D15: J1.28 (S23), J2.19
/XP_D16: J1.9 (S4_D2P), J2.4
/XP_D17: J1.26 (S21), J2.3
GND: C2.2, C3.2, C4.2, C5.2, C6.2, C7.2, C8.2, C9.2, C10.2, C11.2, C12.2, C13.2, C14.2, J1.41 (GND), J2.5, J2.6, J2.17, J2.18, J2.27, J2.28, J2.37, J2.38, J2.41, J2.42, J2.45, J2.47, J2.49, J2.MP (MountPin), J3.6, R8.1, R9.1, U1.2 (GND), U2.8 (GND), U2.21 (GND), U3.3 (GND)
unnamed: C1.1, R3.1, U3.1 (IN+)
unnamed: C1.2, R5.1, U3.2 (IN-)
unnamed: C2.1, C3.1, C4.1, L1.1, R4.2, R5.2
unnamed: R6.1, R8.2, U3.8 (A1)
unnamed: R7.1, R9.2, U3.7 (A0)
